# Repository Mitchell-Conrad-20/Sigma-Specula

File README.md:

# Sigma-Specula
**ECE 420 - Embedded Systems Project** <br>
Smart/Augmented Reality Glasses

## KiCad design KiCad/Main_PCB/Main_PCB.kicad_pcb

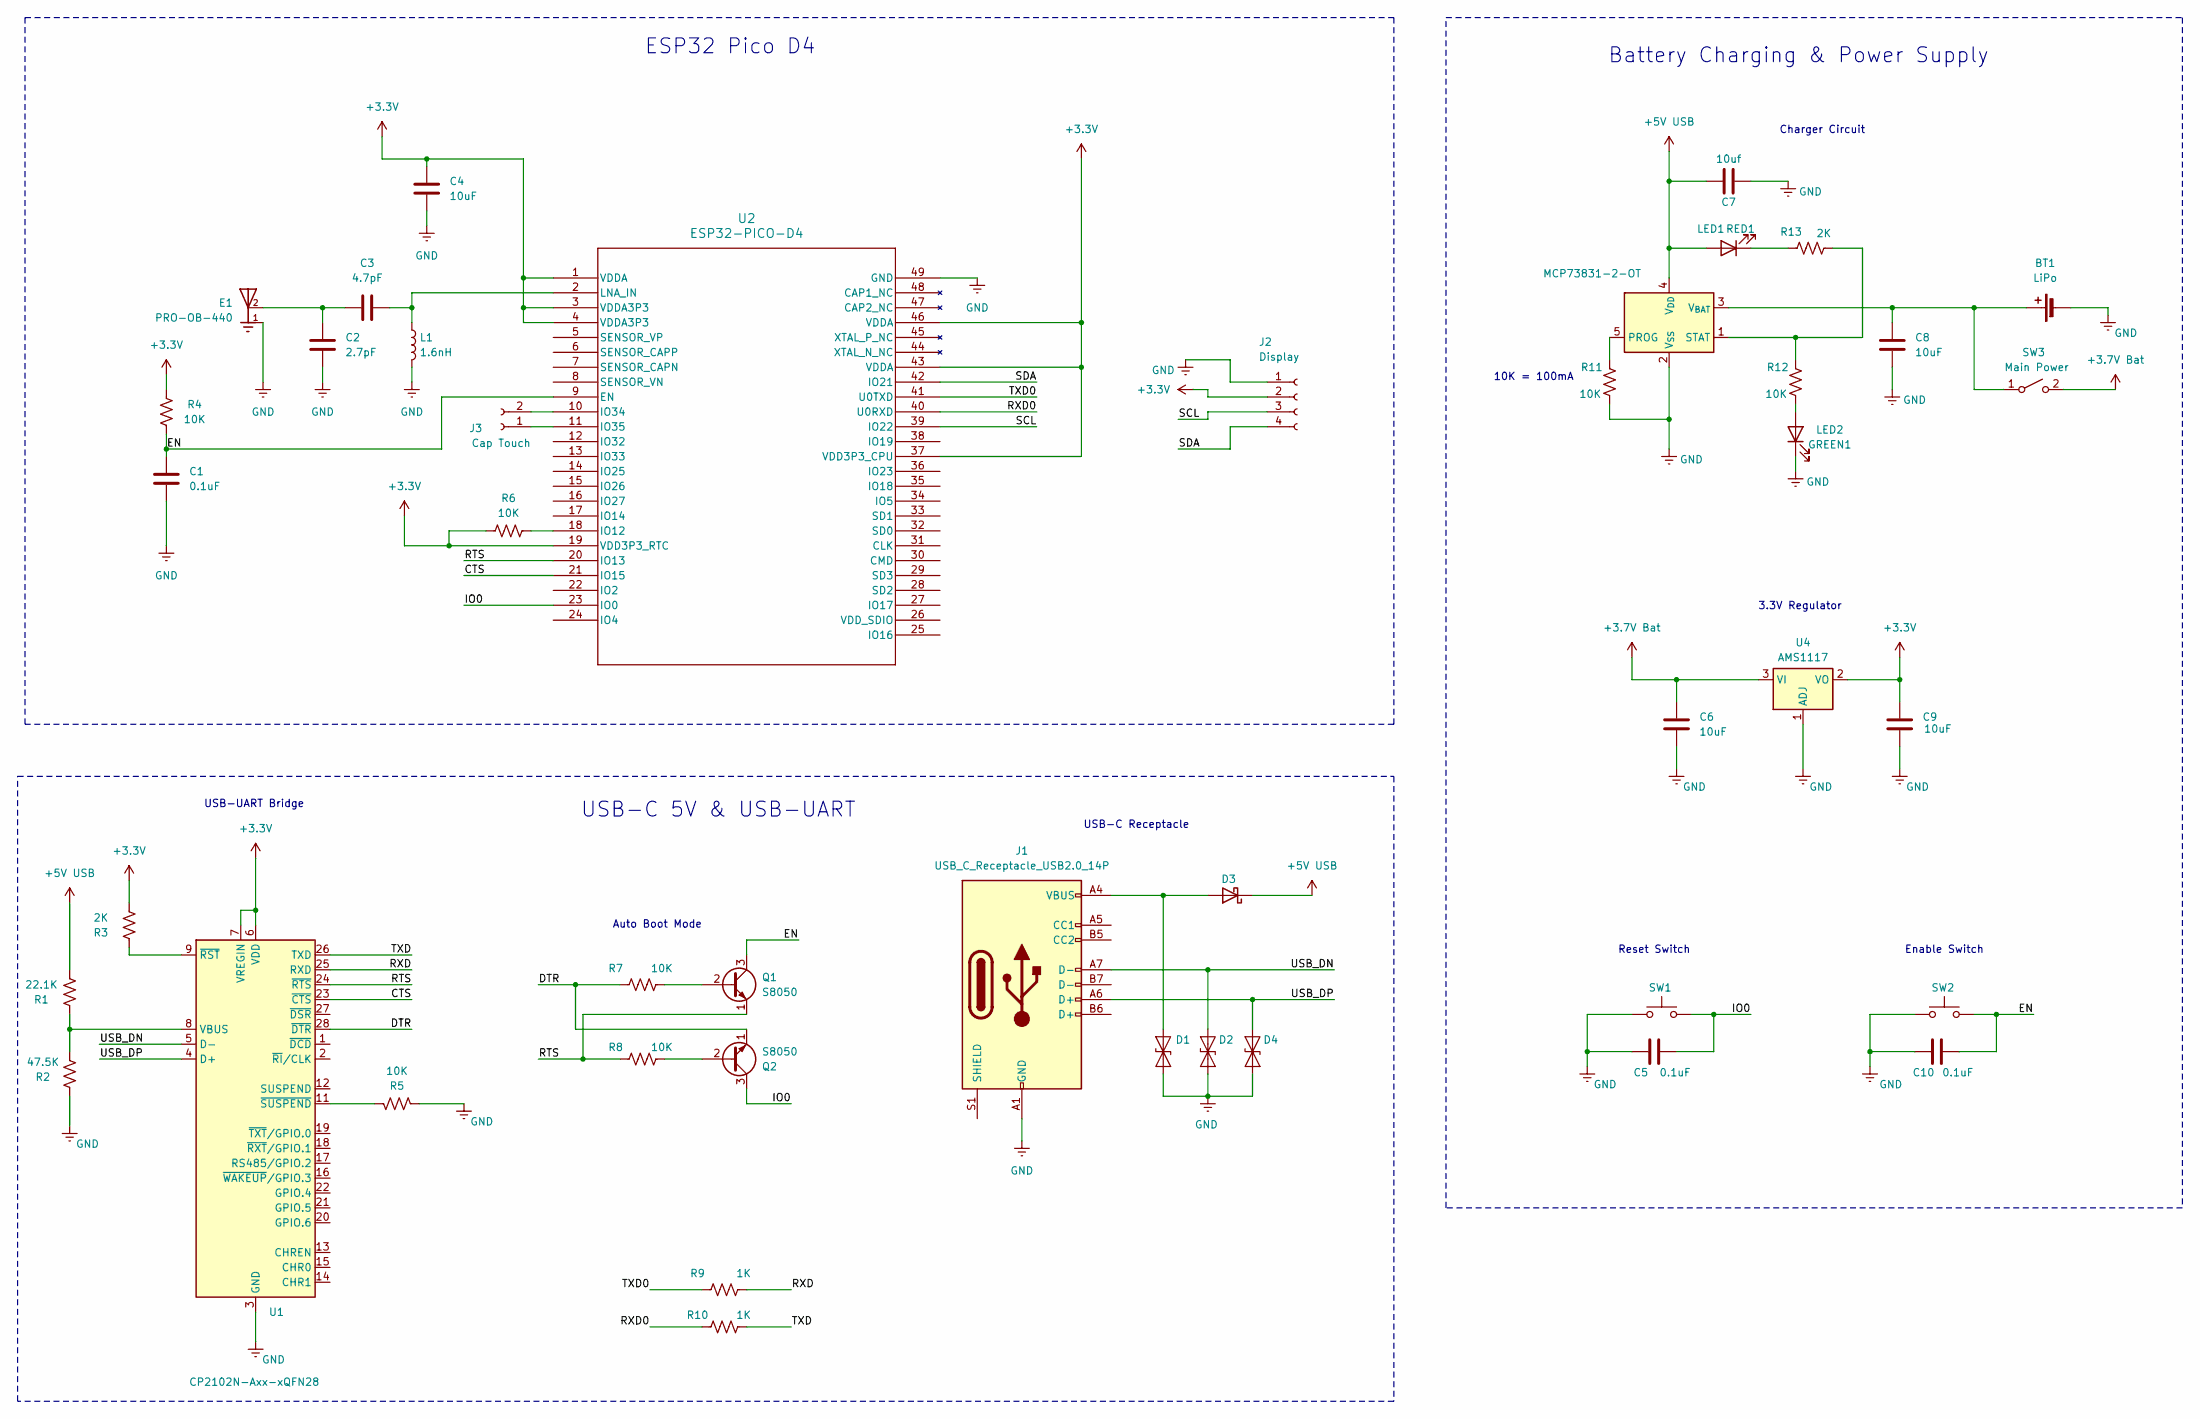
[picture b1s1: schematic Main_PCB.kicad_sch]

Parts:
BT1: LiPo; SolderWire-0.1sqmm_1x02_P3.6mm_D0.4mm_OD1mm
C1, C5, C10: 0.1uF; C_0402_1005Metric; LCSC C141382
C2: 2.7pF; C_0402_1005Metric; LCSC C172851
C3: 4.7pF; C_0402_1005Metric; LCSC C85883
C4, C6, C8, C9: 10uF; C_0402_1005Metric; LCSC C87148
C7: 10uf; C_0402_1005Metric; LCSC C87148
D1, D2, D4: ESD5D5.0CT1G; D_SOD-523; LCSC C5246195
D3: BAT760-7; D_SOD-323; LCSC C124187
E1: PRO-OB-440; Abracon_PRO-OB-440; PARTREV 11-01-22; LCSC C5122736
GREEN1: LED2; LED_0402_1005Metric; LCSC C434449
J1: USB_C_Receptacle_USB2.0_14P; USB_C_Receptacle_GCT_USB4085; LCSC C9900013983
J2: Display; SolderWire-0.1sqmm_1x04_P3.6mm_D0.4mm_OD1mm
J3: Cap Touch; SolderWire-0.1sqmm_1x02_P3.6mm_D0.4mm_OD1mm
L1: 1.6nH; L_0402_1005Metric; LCSC C279912
Q1, Q2: S8050; SOT-23; LCSC C909746
R1: 22.1K; R_0603_1608Metric; LCSC C25961
R2: 47.5K; R_0603_1608Metric; LCSC C23061
R3, R13: 2K; R_0402_1005Metric; LCSC C100608
R4, R5, R6, R7, R8, R11, R12: 10K; R_0402_1005Metric; LCSC C25744
R9, R10: 1K; R_0402_1005Metric; LCSC C138287
RED1: LED1; LED_0402_1005Metric; LCSC C434445
SW1, SW2: SW_Push_SPST_NO_Alps_SKRK; LCSC C115357
SW3: Main Power; SolderWire-0.1sqmm_1x02_P3.6mm_D0.4mm_OD1mm
U1: CP2102N-Axx-xQFN28; QFN-28-1EP_5x5mm_P0.5mm_EP3.35x3.35mm; LCSC C1550553
U2: ESP32-PICO-D4; ESP32-PICO-D4_EXP; LCSC C193707
U3: MCP73831-2-OT; SOT-23-5; LCSC C424093
U4: AMS1117; SOT-223-3_TabPin2; LCSC C6186

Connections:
+3.3V: C4.1, C9.1, J2.2, R3.1, R4.1, R6.1, U1.6 (VDD), U1.7 (VREGIN), U2.1 (VDDA), U2.3 (VDDA3P3), U2.4 (VDDA3P3), U2.19 (VDD3P3_RTC), U2.37 (VDD3P3_CPU), U2.43 (VDDA), U2.46 (VDDA), U4.2 (VO); also elsewhere on the board
+3.7V Bat: C6.1, SW3.2 (B), U4.3 (VI)
+5V USB: C7.2, D3.1 (K), R1.1, RED1.2 (A), U3.4 (V_{DD})
/CTS: U1.23 (~CTS), U2.21 (IO15)
/DTR: Q2.1 (E), R7.2, U1.28 (~DTR)
/EN: C1.1, C10.1, Q1.3 (C), R4.2, SW2.2, U2.9 (EN)
/IO0: C5.1, Q2.3 (C), SW1.2, U2.23 (IO0)
/RTS: Q1.1 (E), R8.2, U1.24 (~RTS), U2.20 (IO13)
/RXD: R9.1, U1.25 (RXD)
/RXD0: R10.2, U2.40 (U0RXD)
/SCL: J2.3, U2.39 (IO22)
/SDA: J2.4, U2.42 (IO21)
/TXD: R10.1, U1.26 (TXD)
/TXD0: R9.2, U2.41 (U0TXD)
/USB_DN: D2.1 (A1), J1.A7 (D-), U1.5 (D-)
/USB_DP: D4.1 (A1), J1.A6 (D+), U1.4 (D+)
GND: BT1.2 (-), C1.2, C2.2, C4.2, C5.2, C6.2, C7.1, C8.2, C9.2, C10.2, D1.2 (A2), D2.2 (A2), D4.2 (A2), E1.1, GREEN1.1 (K), J1.A1 (GND), J1.A12 (GND), J1.B1 (GND), J1.B12 (GND), J2.1, L1.2, R2.2, R5.2, R11.2, SW1.1, SW2.1, U1.3 (GND), U1.29 (GND), U2.49 (GND), U3.2 (V_{SS}), U4.1 (ADJ); also elsewhere on the board
unnamed: BT1.1 (+), C8.1, SW3.1 (A), U3.3 (V_{BAT})
unnamed: C2.1, C3.2, E1.2
unnamed: D1.1 (A1), D3.2 (A), J1.A4 (VBUS), J1.A9 (VBUS), J1.B4 (VBUS), J1.B9 (VBUS)
unnamed: GREEN1.2 (A), R12.2
unnamed: J3.1, U2.11 (IO35)
unnamed: J3.2, U2.10 (IO34)
unnamed: Q1.2 (B), R7.1
unnamed: Q2.2 (B), R8.1
unnamed: R13.2, RED1.1 (K)
unnamed: R1.2, R2.1, U1.8 (VBUS)
unnamed: R3.2, U1.9 (~RST)
unnamed: R5.1, U1.11 (~SUSPEND)
unnamed: R6.2, U2.18 (IO12)
unnamed: C3.1, L1.1, U2.2 (LNA_IN)
unnamed: R11.1, U3.5 (PROG)
unnamed: R12.1, R13.1, U3.1 (STAT)

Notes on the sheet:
Enable Switch
Charger Circuit
USB-C Receptacle
Auto Boot Mode
ESP32 Pico D4
Battery Charging & Power Supply
3.3V Regulator
USB-C 5V & USB-UART
10K = 100mA
USB-UART Bridge
Reset Switch

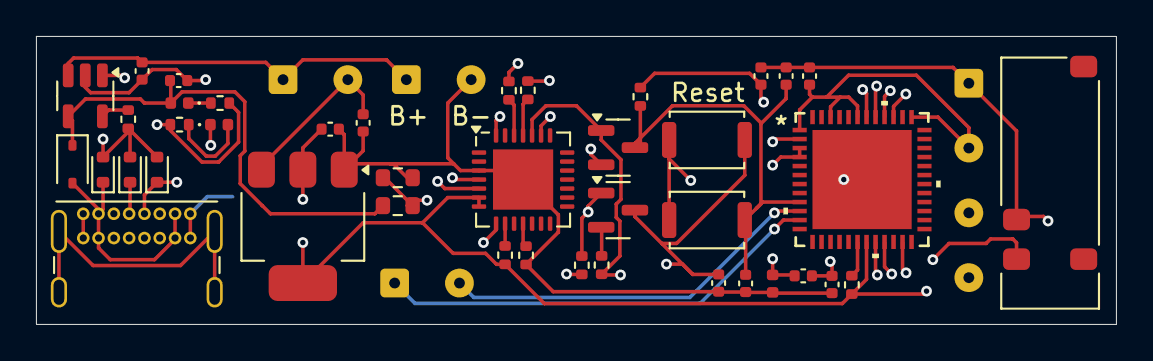
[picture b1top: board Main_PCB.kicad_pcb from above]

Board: 4 copper layers, 60.0 x 16.0 mm, 45 parts (0 on the bottom side), 33 nets.

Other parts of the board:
C4#2: 0.1uF; C_0402_1005Metric

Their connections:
+3.3V: C4#2.1; also elsewhere on the board
GND: C4#2.2; also elsewhere on the board

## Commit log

2024-05-28 Initial code setup
2024-05-28 Get all of the libraries setup to work on platformio
2024-05-29 Add cap touch and quick cap touch
2024-05-29 Created a debug function for quick GUI construction
2024-05-29 Update main for test
2024-05-29 DEBUG Update
2024-06-01 PCB Setup
2024-06-01 Basic Pinout Pico D4
2024-06-01 done editing
2024-06-03 Added 8 and 16 pixel fonts as well as text mirroring code.
2024-06-03 Schematic Progress
    -Added bounding Boxes
    -Some USB-UART Stuff from ESP schematic
2024-06-03 Small update fixing bugs and adding features during class
2024-06-03 push
2024-06-03 Close File
2024-06-04 ANCS testing (and GFX ISSUE)
2024-06-09 Fixed BLE and Display Bug allowing both to work (one at a time at the moment)
2024-06-10 Added text wrapping functions to enable notifications displaying
2024-06-10 Updated PCB
2024-06-13 Added pump charge circuit
2024-06-17 Added charging circuit
2024-07-01 Finished charging circuit
    Need someone to double check and make sure nothing else needs added before work on the pcb design starts
2024-07-01 Closed file
2024-07-03 Cleaned up for Milestone #2
2024-07-08 Fixed ERC errors and added power inputs
2024-07-08 Started PCB
2024-07-08 Changed Footprints
2024-07-10 PCB update
2024-07-10 Most traces done
2024-07-10 Different layout attempt
2024-07-10 Added Ground plane and Migrated Libraries
2024-07-10 Ground plane
2024-07-10 Close
2024-07-11 Pre JLC Check
2024-07-11 Final update
    Added Gerber File and BOM
2024-07-15 Updated for JLCPCB
    - Added BOM
    - Changed Diode footprints
    - added JLC part numbers
    - added cap touch pins
2024-07-15 Added BOM file
2024-07-15 Edit USB silkscreen
2024-08-07 Final Code
